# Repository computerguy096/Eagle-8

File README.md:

# Eagle-8: Pentium Pro for affordable boards

This is a Socket 8 to Slot 1 adapter (so called "slotket") which allows you to install Pentium Pro CPUs in Slot 1 motherboards. This project was mainly started because of the Socket 8 boards scarcity and limitations (no AGP bus, limited to EDO memory, etc) and being tired of having to deal with them. 

Features:
- AM3 bracket holes + 3D printed spacer (modern AM3 CPUs sit lower than the Pentium Pro, so it has to be adapted)
- spot for an optional NTC thermistor located right under the CPU package; it is connected to the J3 header at the top
- spot for an optional 3-pin fan header, fed from the +5V pin in the Slot 1 connector
- FSB jumper with the option to run the slotket at 100MHz bus speed
- BR1<->BR3 selection jumper, to allow dual CPU operation in 440BX boards

There is an interactive HTML BOM which you can find [here](kicad/bom/ibom.html)

Support is experimental at the moment, depending on which CPU you chose.

The Pentium II Overdrive will run on all boards, although it may need microcode updates.

The Pentium Pro (all models) varies depending on the platform.

A list of support for Award based boards (that I have tested so far):
- i440FX/440LX: runs out of the box if BIOS is older than 1998, may need microcodes
- VIA 693/ALi M1621: unlikely to run out of the box; most BIOSes are >=1998
- i440BX: has ACPI bugs, same problems as above
- i810/815: unlikely to run due to incompatible VRM spec, same problems as above

A few select ASUS boards received experimental patched BIOSes, which were kindly provided by Deniz Özmen on his [website](https://oezmen.eu/bios/), though keep in mind your mileage may vary.

For manufacturing, ENIG plating is highly recommended.

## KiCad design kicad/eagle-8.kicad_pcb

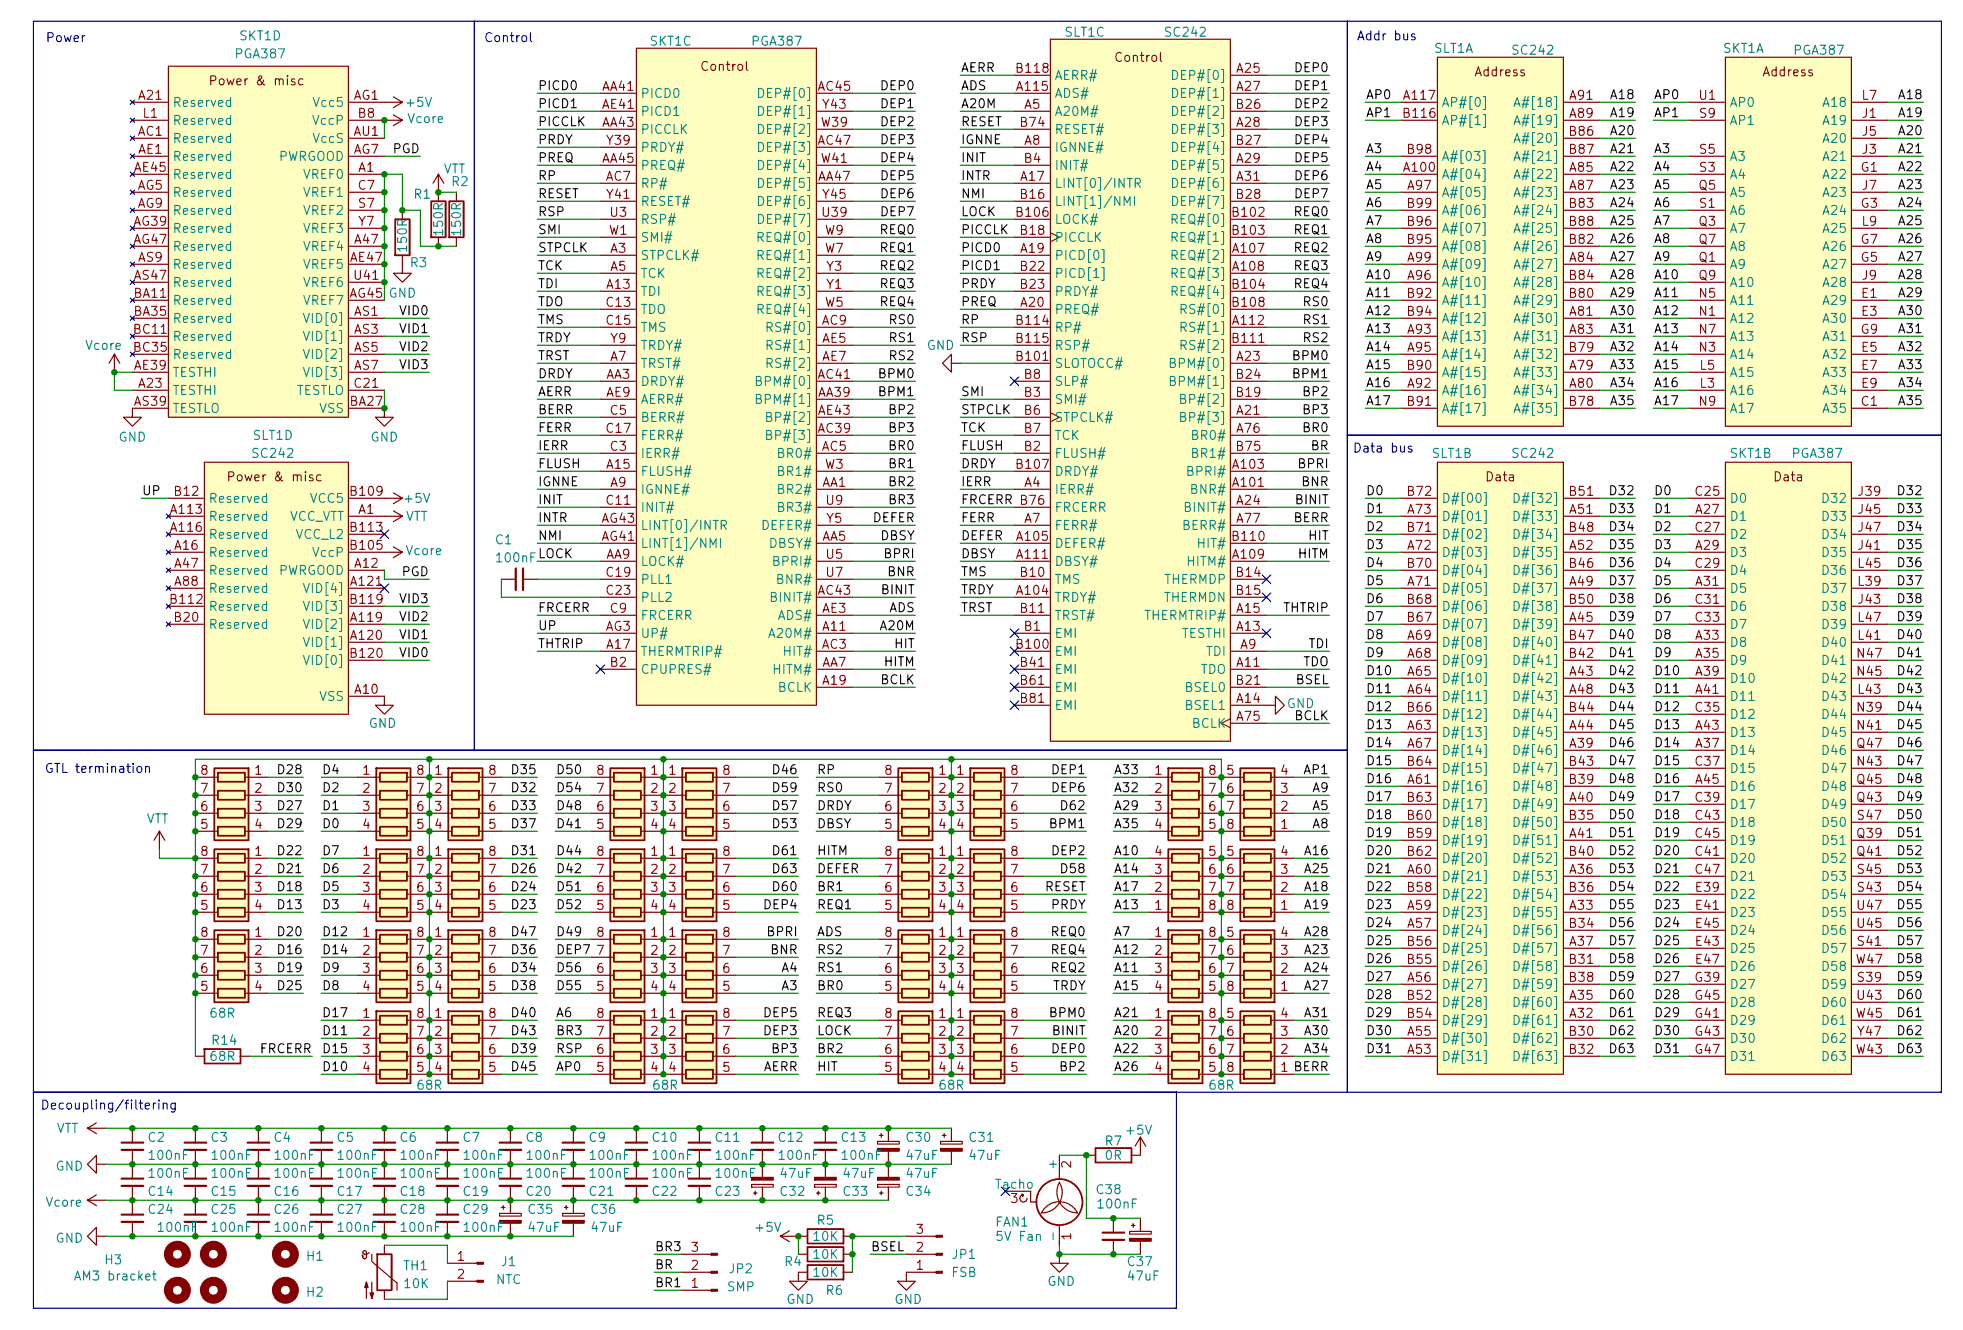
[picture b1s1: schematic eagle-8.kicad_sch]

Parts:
C1, C2: 100nF; C_0805_2012Metric; LCSC C1711
C3, C4, C5, C6, C7, C8, C9, C10, C11, C12, C13, C14, C15, C16, C17, C18, C19, C20, C21, C22, C23, C24, C25, C26, C27, C28, C29, C38: 100nF; C_0805_2012Metric
C30, C31, C32, C33, C34, C35, C37: 47uF; CP_EIA-7343-40_Kemet-Y_HandSolder
C36: 47uF; CP_EIA-7343-40_Kemet-Y_HandSolder; LCSC C600546
FAN1: 5V Fan; FanPinHeader_1x03_P2.54mm_Vertical
H1, H2: MountingHole; MountingHole_3.2mm_M3_DIN965
H3: AM3 bracket
J1: NTC; PinHeader_1x02_P2.54mm_Vertical
JP1: FSB; PinHeader_1x03_P2.54mm_Vertical
JP2: SMP; PinHeader_1x03_P2.54mm_Vertical
R1, R2, R3: 150R; R_0805_2012Metric; LCSC C17471
R4, R5, R6: 10K; R_0805_2012Metric; LCSC C17414
R7: 0R; R_0805_2012Metric; LCSC C17477
R14: 68R; R_0805_2012Metric; LCSC C17802
RN1, RN2, RN3, RN4, RN5, RN6, RN7, RN8, RN9, RN10, RN11, RN13, RN14, RN15, RN16, RN17, RN18, RN19, RN20, RN21, RN22, RN23, RN24, RN25, RN26, RN27, RN28, RN29, RN30, RN31, RN32, RN33, RN34, RN35: 68R; VTT array
RN12: 68R; VTT array; LCSC C429297
SKT1: PGA387
SLT1: SC242; Slot 1
TH1: 10K; PinHeader_1x02_P2.54mm_Vertical

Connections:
+5V: R4.1, R5.1, R7.2, SKT1.AG1 (Vcc5), SLT1.B109 (VCC5)
/A3: RN31.5 (R4.2), SKT1.S5 (A3), SLT1.B98 (A#[03])
/A4: RN31.6 (R3.2), SKT1.S3 (A4), SLT1.A100 (A#[04])
/A5: RN1.2 (R2.1), SKT1.Q5 (A5), SLT1.A97 (A#[05])
/A6: RN35.8 (R1.2), SKT1.S1 (A6), SLT1.B99 (A#[06])
/A7: RN4.1 (R1.1), SKT1.Q3 (A7), SLT1.B96 (A#[07])
/A8: RN1.1 (R1.1), SKT1.Q7 (A8), SLT1.B95 (A#[08])
/A9: RN1.3 (R3.1), SKT1.Q1 (A9), SLT1.A99 (A#[09])
/A10: RN2.4 (R4.1), SKT1.Q9 (A10), SLT1.A96 (A#[10])
/A11: RN4.3 (R3.1), SKT1.N5 (A11), SLT1.B92 (A#[11])
/A12: RN4.2 (R2.1), SKT1.N1 (A12), SLT1.B94 (A#[12])
/A13: RN2.1 (R1.1), SKT1.N7 (A13), SLT1.A93 (A#[13])
/A14: RN2.3 (R3.1), SKT1.N3 (A14), SLT1.A95 (A#[14])
/A15: RN4.4 (R4.1), SKT1.L5 (A15), SLT1.B90 (A#[15])
/A16: RN3.4 (R4.1), SKT1.L3 (A16), SLT1.A92 (A#[16])
/A17: RN2.2 (R2.1), SKT1.N9 (A17), SLT1.B91 (A#[17])
/A18: RN3.2 (R2.1), SKT1.L7 (A18), SLT1.A91 (A#[18])
/A19: RN3.1 (R1.1), SKT1.J1 (A19), SLT1.A89 (A#[19])
/A20: RN6.2 (R2.1), SKT1.J5 (A20), SLT1.B86 (A#[20])
/A20M: SKT1.A11 (A20M#), SLT1.A5 (A20M#)
/A21: RN6.1 (R1.1), SKT1.J3 (A21), SLT1.B87 (A#[21])
/A22: RN6.3 (R3.1), SKT1.G1 (A22), SLT1.A85 (A#[22])
/A23: RN5.3 (R3.1), SKT1.J7 (A23), SLT1.A87 (A#[23])
/A24: RN5.2 (R2.1), SKT1.G3 (A24), SLT1.B83 (A#[24])
/A25: RN3.3 (R3.1), SKT1.L9 (A25), SLT1.B88 (A#[25])
/A26: RN6.4 (R4.1), SKT1.G7 (A26), SLT1.B82 (A#[26])
/A27: RN5.1 (R1.1), SKT1.G5 (A27), SLT1.A84 (A#[27])
/A28: RN5.4 (R4.1), SKT1.J9 (A28), SLT1.B84 (A#[28])
/A29: RN24.3 (R3.1), SKT1.E1 (A29), SLT1.B80 (A#[29])
/A30: RN7.3 (R3.1), SKT1.E3 (A30), SLT1.A81 (A#[30])
/A31: RN7.4 (R4.1), SKT1.G9 (A31), SLT1.A83 (A#[31])
/A32: RN24.2 (R2.1), SKT1.E5 (A32), SLT1.B79 (A#[32])
/A33: RN24.1 (R1.1), SKT1.E7 (A33), SLT1.A79 (A#[33])
/A34: RN7.2 (R2.1), SKT1.E9 (A34), SLT1.A80 (A#[34])
/A35: RN24.4 (R4.1), SKT1.C1 (A35), SLT1.B78 (A#[35])
/ADS: RN29.8 (R1.2), SKT1.AE3 (ADS#), SLT1.A115 (ADS#)
/AERR: RN32.5 (R4.2), SKT1.AE9 (AERR#), SLT1.B118 (AERR#)
/AP0: RN35.5 (R4.2), SKT1.U1 (AP0), SLT1.A117 (AP#[0])
/AP1: RN1.4 (R4.1), SKT1.S9 (AP1), SLT1.B116 (AP#[1])
/BCLK: SKT1.A19 (BCLK), SLT1.A75 (BCLK)
/BERR: RN7.1 (R1.1), SKT1.C5 (BERR#), SLT1.A77 (BERR#)
/BINIT: RN28.7 (R2.2), SKT1.AC43 (BINIT#), SLT1.A24 (BINIT#)
/BNR: RN31.7 (R2.2), SKT1.U7 (BNR#), SLT1.A101 (BNR#)
/BP2: RN28.5 (R4.2), SKT1.AE43 (BP#[2]), SLT1.B19 (BP#[2])
/BP3: RN32.6 (R3.2), SKT1.AC39 (BP#[3]), SLT1.A21 (BP#[3])
/BPM0: RN28.8 (R1.2), SKT1.AC41 (BPM#[0]), SLT1.A23 (BPM#[0])
/BPM1: RN25.5 (R4.2), SKT1.AA39 (BPM#[1]), SLT1.B24 (BPM#[1])
/BPRI: RN31.8 (R1.2), SKT1.U5 (BPRI#), SLT1.A103 (BPRI#)
/BR: JP2.2, SLT1.B75 (BR1#)
/BR0: RN29.5 (R4.2), SKT1.AC5 (BR0#), SLT1.A76 (BR0#)
/BR1: JP2.1, RN34.6 (R3.2), SKT1.W3 (BR1#)
/BR2: RN30.6 (R3.2), SKT1.AA1 (BR2#)
/BR3: JP2.3, RN35.7 (R2.2), SKT1.U9 (BR3#)
/BSEL: JP1.2, SLT1.B21 (BSEL0)
/D0: RN8.4 (R4.1), SKT1.C25 (D0), SLT1.B72 (D#[00])
/D1: RN8.3 (R3.1), SKT1.A27 (D1), SLT1.A73 (D#[01])
/D2: RN8.2 (R2.1), SKT1.C27 (D2), SLT1.B71 (D#[02])
/D3: RN9.4 (R4.1), SKT1.A29 (D3), SLT1.A72 (D#[03])
/D4: RN8.1 (R1.1), SKT1.C29 (D4), SLT1.B70 (D#[04])
/D5: RN9.3 (R3.1), SKT1.A31 (D5), SLT1.A71 (D#[05])
/D6: RN9.2 (R2.1), SKT1.C31 (D6), SLT1.B68 (D#[06])
/D7: RN9.1 (R1.1), SKT1.C33 (D7), SLT1.B67 (D#[07])
/D8: RN10.4 (R4.1), SKT1.A33 (D8), SLT1.A69 (D#[08])
/D9: RN10.3 (R3.1), SKT1.A35 (D9), SLT1.A68 (D#[09])
/D10: RN11.4 (R4.1), SKT1.A39 (D10), SLT1.A65 (D#[10])
/D11: RN11.2 (R2.1), SKT1.A41 (D11), SLT1.A64 (D#[11])
/D12: RN10.1 (R1.1), SKT1.C35 (D12), SLT1.B66 (D#[12])
/D13: RN13.4 (R4.1), SKT1.A43 (D13), SLT1.A63 (D#[13])
/D14: RN10.2 (R2.1), SKT1.A37 (D14), SLT1.A67 (D#[14])
/D15: RN11.3 (R3.1), SKT1.C37 (D15), SLT1.B64 (D#[15])
/D16: RN14.2 (R2.1), SKT1.A45 (D16), SLT1.A61 (D#[16])
/D17: RN11.1 (R1.1), SKT1.C39 (D17), SLT1.B63 (D#[17])
/D18: RN13.3 (R3.1), SKT1.C43 (D18), SLT1.B60 (D#[18])
/D19: RN14.3 (R3.1), SKT1.C45 (D19), SLT1.B59 (D#[19])
/D20: RN14.1 (R1.1), SKT1.C41 (D20), SLT1.B62 (D#[20])
/D21: RN13.2 (R2.1), SKT1.C47 (D21), SLT1.A60 (D#[21])
/D22: RN13.1 (R1.1), SKT1.E39 (D22), SLT1.B58 (D#[22])
/D23: RN16.5 (R4.2), SKT1.E41 (D23), SLT1.A59 (D#[23])
/D24: RN16.6 (R3.2), SKT1.E45 (D24), SLT1.A57 (D#[24])
/D25: RN14.4 (R4.1), SKT1.E43 (D25), SLT1.B56 (D#[25])
/D26: RN16.7 (R2.2), SKT1.E47 (D26), SLT1.B55 (D#[26])
/D27: RN12.3 (R3.1), SKT1.G39 (D27), SLT1.A56 (D#[27])
/D28: RN12.1 (R1.1), SKT1.G45 (D28), SLT1.B52 (D#[28])
/D29: RN12.4 (R4.1), SKT1.G41 (D29), SLT1.B54 (D#[29])
/D30: RN12.2 (R2.1), SKT1.G43 (D30), SLT1.A55 (D#[30])
/D31: RN16.8 (R1.2), SKT1.G47 (D31), SLT1.A53 (D#[31])
/D32: RN15.7 (R2.2), SKT1.J39 (D32), SLT1.B51 (D#[32])
/D33: RN15.6 (R3.2), SKT1.J45 (D33), SLT1.A51 (D#[33])
/D34: RN17.6 (R3.2), SKT1.J47 (D34), SLT1.B48 (D#[34])
/D35: RN15.8 (R1.2), SKT1.J41 (D35), SLT1.A52 (D#[35])
/D36: RN17.7 (R2.2), SKT1.L45 (D36), SLT1.B46 (D#[36])
/D37: RN15.5 (R4.2), SKT1.L39 (D37), SLT1.A49 (D#[37])
/D38: RN17.5 (R4.2), SKT1.J43 (D38), SLT1.B50 (D#[38])
/D39: RN18.6 (R3.2), SKT1.L47 (D39), SLT1.A45 (D#[39])
/D40: RN18.8 (R1.2), SKT1.L41 (D40), SLT1.B47 (D#[40])
/D41: RN19.5 (R4.2), SKT1.N47 (D41), SLT1.B42 (D#[41])
/D42: RN20.7 (R2.2), SKT1.N45 (D42), SLT1.A43 (D#[42])
/D43: RN18.7 (R2.2), SKT1.L43 (D43), SLT1.A48 (D#[43])
/D44: RN20.8 (R1.2), SKT1.N39 (D44), SLT1.B44 (D#[44])
/D45: RN18.5 (R4.2), SKT1.N41 (D45), SLT1.A44 (D#[45])
/D46: RN22.8 (R1.2), SKT1.Q47 (D46), SLT1.A39 (D#[46])
/D47: RN17.8 (R1.2), SKT1.N43 (D47), SLT1.B43 (D#[47])
/D48: RN19.6 (R3.2), SKT1.Q45 (D48), SLT1.B39 (D#[48])
/D49: RN21.8 (R1.2), SKT1.Q43 (D49), SLT1.A40 (D#[49])
/D50: RN19.8 (R1.2), SKT1.S47 (D50), SLT1.B35 (D#[50])
/D51: RN20.6 (R3.2), SKT1.Q39 (D51), SLT1.A41 (D#[51])
/D52: RN20.5 (R4.2), SKT1.Q41 (D52), SLT1.B40 (D#[52])
/D53: RN22.5 (R4.2), SKT1.S45 (D53), SLT1.A36 (D#[53])
/D54: RN19.7 (R2.2), SKT1.S43 (D54), SLT1.B36 (D#[54])
/D55: RN21.5 (R4.2), SKT1.U47 (D55), SLT1.A33 (D#[55])
/D56: RN21.6 (R3.2), SKT1.U45 (D56), SLT1.B34 (D#[56])
/D57: RN22.6 (R3.2), SKT1.S41 (D57), SLT1.A37 (D#[57])
/D58: RN26.7 (R2.2), SKT1.W47 (D58), SLT1.B31 (D#[58])
/D59: RN22.7 (R2.2), SKT1.S39 (D59), SLT1.B38 (D#[59])
/D60: RN23.6 (R3.2), SKT1.U43 (D60), SLT1.A35 (D#[60])
/D61: RN23.8 (R1.2), SKT1.W45 (D61), SLT1.A32 (D#[61])
/D62: RN25.6 (R3.2), SKT1.Y47 (D62), SLT1.B30 (D#[62])
/D63: RN23.7 (R2.2), SKT1.W43 (D63), SLT1.B32 (D#[63])
/DBSY: RN33.5 (R4.2), SKT1.AA5 (DBSY#), SLT1.A111 (DBSY#)
/DEFER: RN34.7 (R2.2), SKT1.Y5 (DEFER#), SLT1.A105 (DEFER#)
/DEP0: RN28.6 (R3.2), SKT1.AC45 (DEP#[0]), SLT1.A25 (DEP#[0])
/DEP1: RN25.8 (R1.2), SKT1.Y43 (DEP#[1]), SLT1.A27 (DEP#[1])
/DEP2: RN26.8 (R1.2), SKT1.W39 (DEP#[2]), SLT1.B26 (DEP#[2])
/DEP3: RN32.7 (R2.2), SKT1.AC47 (DEP#[3]), SLT1.A28 (DEP#[3])
/DEP4: RN23.5 (R4.2), SKT1.W41 (DEP#[4]), SLT1.B27 (DEP#[4])
/DEP5: RN32.8 (R1.2), SKT1.AA47 (DEP#[5]), SLT1.A29 (DEP#[5])
/DEP6: RN25.7 (R2.2), SKT1.Y45 (DEP#[6]), SLT1.A31 (DEP#[6])
/DEP7: RN21.7 (R2.2), SKT1.U39 (DEP#[7]), SLT1.B28 (DEP#[7])
/DRDY: RN33.6 (R3.2), SKT1.AA3 (DRDY#), SLT1.B107 (DRDY#)
/FERR: SKT1.C17 (FERR#), SLT1.A7 (FERR#)
/FLUSH: SKT1.A15 (FLUSH#), SLT1.B2 (FLUSH#)
/FRCERR: R14.1, SKT1.C9 (FRCERR), SLT1.B76 (FRCERR)
/HIT: RN30.5 (R4.2), SKT1.AC3 (HIT#), SLT1.B110 (HIT#)
/HITM: RN34.8 (R1.2), SKT1.AA7 (HITM#), SLT1.A109 (HITM#)
/IERR: SKT1.C3 (IERR#), SLT1.A4 (IERR#)
/IGNNE: SKT1.A9 (IGNNE#), SLT1.A8 (IGNNE#)
/INIT: SKT1.C11 (INIT#), SLT1.B4 (INIT#)
/INTR: SKT1.AG43 (LINT[0]/INTR), SLT1.A17 (LINT[0]/INTR)
/LOCK: RN30.7 (R2.2), SKT1.AA9 (LOCK#), SLT1.B106 (LOCK#)
/NMI: SKT1.AG41 (LINT[1]/NMI), SLT1.B16 (LINT[1]/NMI)
/PGD: SKT1.AG7 (PWRGOOD), SLT1.A12 (PWRGOOD)
/PICCLK: SKT1.AA43 (PICCLK), SLT1.B18 (PICCLK)
/PICD0: SKT1.AA41 (PICD0), SLT1.A19 (PICD[0])
/PICD1: SKT1.AE41 (PICD1), SLT1.B22 (PICD[1])
/PRDY: RN26.5 (R4.2), SKT1.Y39 (PRDY#), SLT1.B23 (PRDY#)
/PREQ: SKT1.AA45 (PREQ#), SLT1.A20 (PREQ#)
/REQ0: RN27.8 (R1.2), SKT1.W9 (REQ#[0]), SLT1.B102 (REQ#[0])
/REQ1: RN34.5 (R4.2), SKT1.W7 (REQ#[1]), SLT1.B103 (REQ#[1])
/REQ2: RN27.6 (R3.2), SKT1.Y3 (REQ#[2]), SLT1.A107 (REQ#[2])
/REQ3: RN30.8 (R1.2), SKT1.Y1 (REQ#[3]), SLT1.A108 (REQ#[3])
/REQ4: RN27.7 (R2.2), SKT1.W5 (REQ#[4]), SLT1.B104 (REQ#[4])
/RESET: RN26.6 (R3.2), SKT1.Y41 (RESET#), SLT1.B74 (RESET#)
/RP: RN33.8 (R1.2), SKT1.AC7 (RP#), SLT1.B114 (RP#)
/RS0: RN33.7 (R2.2), SKT1.AC9 (RS#[0]), SLT1.B108 (RS#[0])
/RS1: RN29.6 (R3.2), SKT1.AE5 (RS#[1]), SLT1.A112 (RS#[1])
/RS2: RN29.7 (R2.2), SKT1.AE7 (RS#[2]), SLT1.B111 (RS#[2])
/RSP: RN35.6 (R3.2), SKT1.U3 (RSP#), SLT1.B115 (RSP#)
/SMI: SKT1.W1 (SMI#), SLT1.B3 (SMI#)
/STPCLK: SKT1.A3 (STPCLK#), SLT1.B6 (STPCLK#)
/TCK: SKT1.A5 (TCK), SLT1.B7 (TCK)
/TDI: SKT1.A13 (TDI), SLT1.A9 (TDI)
/TDO: SKT1.C13 (TDO), SLT1.A11 (TDO)
/THTRIP: SKT1.A17 (THERMTRIP#), SLT1.A15 (THERMTRIP#)
/TMS: SKT1.C15 (TMS), SLT1.B10 (TMS)
/TRDY: RN27.5 (R4.2), SKT1.Y9 (TRDY#), SLT1.A104 (TRDY#)
/TRST: SKT1.A7 (TRST#), SLT1.B11 (TRST#)
/UP: SKT1.AG3 (UP#), SLT1.B12 (Reserved)
/VID0: SKT1.AS1 (VID[0]), SLT1.B120 (VID[0])
/VID1: SKT1.AS3 (VID[1]), SLT1.A120 (VID[1])
/VID2: SKT1.AS5 (VID[2]), SLT1.A119 (VID[2])
/VID3: SKT1.AS7 (VID[3]), SLT1.B119 (VID[3])
GND: C2.1, C3.1, C4.1, C5.1, C6.1, C7.1, C8.1, C9.1, C10.1, C11.1, C12.1, C13.1, C14.1, C15.1, C16.1, C17.1, C18.1, C19.1, C20.1, C21.1, C22.1, C23.1, C24.1, C25.1, C26.1, C27.1, C28.1, C29.1, C30.2, C31.2, C32.2, C33.2, C34.2, C35.2, C36.2, C37.2, C38.1, FAN1.1 (-), JP1.1, R3.2, R6.1, SKT1.AB2 (VSS), SKT1.AB6 (VSS), SKT1.AB8 (VSS), SKT1.AB40 (VSS), SKT1.AB42 (VSS), SKT1.AB46 (VSS), SKT1.AF2 (VSS), SKT1.AF4 (VSS), SKT1.AF6 (VSS), SKT1.AF8 (VSS), SKT1.AF40 (VSS), SKT1.AF42 (VSS), SKT1.AF44 (VSS), SKT1.AF46 (VSS), SKT1.AJ1 (VSS), SKT1.AJ5 (VSS), SKT1.AJ9 (VSS), SKT1.AJ39 (VSS), SKT1.AJ43 (VSS), SKT1.AJ47 (VSS), SKT1.AL3 (VSS), SKT1.AL7 (VSS), SKT1.AL41 (VSS), SKT1.AL45 (VSS), SKT1.AN1 (VSS), SKT1.AN5 (VSS), SKT1.AN9 (VSS), SKT1.AN39 (VSS), SKT1.AN43 (VSS), SKT1.AN47 (VSS), SKT1.AQ3 (VSS), SKT1.AQ7 (VSS), SKT1.AQ41 (VSS), SKT1.AQ45 (VSS), SKT1.AS39 (TESTLO), SKT1.AS41 (TESTLO), SKT1.AS43 (TESTLO), SKT1.AS45 (TESTLO), SKT1.AU3 (VSS), SKT1.AU7 (VSS), SKT1.AU41 (VSS), SKT1.AU45 (VSS), SKT1.AW1 (VSS), SKT1.AW5 (VSS), SKT1.AW9 (VSS), SKT1.AW39 (VSS), SKT1.AW43 (VSS), SKT1.AW47 (VSS), SKT1.B6 (VSS), SKT1.B12 (VSS), SKT1.B20 (VSS), SKT1.B28 (VSS), SKT1.B36 (VSS), SKT1.B42 (VSS), SKT1.B46 (VSS), SKT1.BA1 (VSS), SKT1.BA5 (VSS), SKT1.BA9 (VSS), SKT1.BA13 (TESTLO), SKT1.BA15 (TESTLO), SKT1.BA19 (VSS), SKT1.BA23 (VSS), SKT1.BA27 (VSS), SKT1.BA31 (VSS), SKT1.BA33 (TESTLO), SKT1.BA37 (TESTLO), SKT1.BA39 (VSS), SKT1.BA43 (VSS), SKT1.BA47 (VSS), SKT1.BC1 (VSS), SKT1.BC3 (VSS), SKT1.BC5 (VSS), SKT1.BC7 (VSS), SKT1.BC9 (VSS), SKT1.BC13 (TESTLO), SKT1.BC15 (TESTLO), SKT1.BC17 (VSS), SKT1.BC21 (VSS), SKT1.BC25 (VSS), SKT1.BC29 (VSS), SKT1.BC33 (TESTLO), SKT1.BC37 (TESTLO), SKT1.BC39 (VSS), SKT1.BC41 (VSS), SKT1.BC43 (VSS), SKT1.BC45 (VSS), SKT1.BC47 (VSS), SKT1.C21 (TESTLO), SKT1.F4 (VSS), SKT1.F8 (VSS), SKT1.F40 (VSS), SKT1.F44 (VSS), SKT1.K2 (VSS), SKT1.K6 (VSS), SKT1.K8 (VSS), SKT1.K40 (VSS), SKT1.K42 (VSS), SKT1.K46 (VSS), SKT1.P4 (VSS), SKT1.P8 (VSS), SKT1.P40 (VSS), SKT1.P44 (VSS), SKT1.T2 (VSS), SKT1.T6 (VSS), SKT1.T8 (VSS), SKT1.T40 (VSS), SKT1.T42 (VSS), SKT1.T46 (VSS), SKT1.X2 (VSS), SKT1.X4 (VSS), SKT1.X8 (VSS), SKT1.X40 (VSS), SKT1.X44 (VSS), SKT1.X46 (VSS), SLT1.A2 (VSS), SLT1.A6 (VSS), SLT1.A10 (VSS), SLT1.A14 (BSEL1), SLT1.A18 (VSS), SLT1.A22 (VSS), SLT1.A26 (VSS), SLT1.A30 (VSS), SLT1.A34 (VSS), SLT1.A38 (VSS), SLT1.A42 (VSS), SLT1.A46 (VSS), SLT1.A50 (VSS), SLT1.A54 (VSS), SLT1.A58 (VSS), SLT1.A62 (VSS), SLT1.A66 (VSS), SLT1.A70 (VSS), SLT1.A74 (VSS), SLT1.A78 (VSS), SLT1.A82 (VSS), SLT1.A86 (VSS), SLT1.A90 (VSS), SLT1.A94 (VSS), SLT1.A98 (VSS), SLT1.A102 (VSS), SLT1.A106 (VSS), SLT1.A110 (VSS), SLT1.A114 (VSS), SLT1.A118 (VSS), SLT1.B101 (SLOTOCC#)
unnamed: C37.1, C38.2, FAN1.2 (+), R7.1
unnamed: J1.1, TH1.1
unnamed: J1.2, TH1.2
unnamed: JP1.3, R4.2, R5.2, R6.2
unnamed: C1.2, SKT1.C19 (PLL1)
unnamed: C1.1, SKT1.C23 (PLL2)
unnamed: R1.2, R2.2, R3.1, SKT1.A1 (VREF0), SKT1.A47 (VREF4), SKT1.AE47 (VREF5), SKT1.AG45 (VREF7), SKT1.C7 (VREF1), SKT1.S7 (VREF2), SKT1.U41 (VREF6), SKT1.Y7 (VREF3)
VTT: C2.2, C3.2, C4.2, C5.2, C6.2, C7.2, C8.2, C9.2, C10.2, C11.2, C12.2, C13.2, C30.1, C31.1, R1.1, R2.1, R14.2, RN1.5 (R4.2), RN1.6 (R3.2), RN1.7 (R2.2), RN1.8 (R1.2), RN2.5 (R4.2), RN2.6 (R3.2), RN2.7 (R2.2), RN2.8 (R1.2), RN3.5 (R4.2), RN3.6 (R3.2), RN3.7 (R2.2), RN3.8 (R1.2), RN4.5 (R4.2), RN4.6 (R3.2), RN4.7 (R2.2), RN4.8 (R1.2), RN5.5 (R4.2), RN5.6 (R3.2), RN5.7 (R2.2), RN5.8 (R1.2), RN6.5 (R4.2), RN6.6 (R3.2), RN6.7 (R2.2), RN6.8 (R1.2), RN7.5 (R4.2), RN7.6 (R3.2), RN7.7 (R2.2), RN7.8 (R1.2), RN8.5 (R4.2), RN8.6 (R3.2), RN8.7 (R2.2), RN8.8 (R1.2), RN9.5 (R4.2), RN9.6 (R3.2), RN9.7 (R2.2), RN9.8 (R1.2), RN10.5 (R4.2), RN10.6 (R3.2), RN10.7 (R2.2), RN10.8 (R1.2), RN11.5 (R4.2), RN11.6 (R3.2), RN11.7 (R2.2), RN11.8 (R1.2), RN12.5 (R4.2), RN12.6 (R3.2), RN12.7 (R2.2), RN12.8 (R1.2), RN13.5 (R4.2), RN13.6 (R3.2), RN13.7 (R2.2), RN13.8 (R1.2), RN14.5 (R4.2), RN14.6 (R3.2), RN14.7 (R2.2), RN14.8 (R1.2), RN15.1 (R1.1), RN15.2 (R2.1), RN15.3 (R3.1), RN15.4 (R4.1), RN16.1 (R1.1), RN16.2 (R2.1), RN16.3 (R3.1), RN16.4 (R4.1), RN17.1 (R1.1), RN17.2 (R2.1), RN17.3 (R3.1), RN17.4 (R4.1), RN18.1 (R1.1), RN18.2 (R2.1), RN18.3 (R3.1), RN18.4 (R4.1), RN19.1 (R1.1), RN19.2 (R2.1), RN19.3 (R3.1), RN19.4 (R4.1), RN20.1 (R1.1), RN20.2 (R2.1), RN20.3 (R3.1), RN20.4 (R4.1), RN21.1 (R1.1), RN21.2 (R2.1), RN21.3 (R3.1), RN21.4 (R4.1), RN22.1 (R1.1), RN22.2 (R2.1), RN22.3 (R3.1), RN22.4 (R4.1), RN23.1 (R1.1), RN23.2 (R2.1), RN23.3 (R3.1), RN23.4 (R4.1), RN24.5 (R4.2), RN24.6 (R3.2), RN24.7 (R2.2), RN24.8 (R1.2), RN25.1 (R1.1), RN25.2 (R2.1), RN25.3 (R3.1), RN25.4 (R4.1), RN26.1 (R1.1), RN26.2 (R2.1), RN26.3 (R3.1), RN26.4 (R4.1), RN27.1 (R1.1), RN27.2 (R2.1), RN27.3 (R3.1), RN27.4 (R4.1), RN28.1 (R1.1), RN28.2 (R2.1), RN28.3 (R3.1), RN28.4 (R4.1), RN29.1 (R1.1), RN29.2 (R2.1), RN29.3 (R3.1), RN29.4 (R4.1), RN30.1 (R1.1), RN30.2 (R2.1), RN30.3 (R3.1), RN30.4 (R4.1), RN31.1 (R1.1), RN31.2 (R2.1), RN31.3 (R3.1), RN31.4 (R4.1), RN32.1 (R1.1), RN32.2 (R2.1), RN32.3 (R3.1), RN32.4 (R4.1), RN33.1 (R1.1), RN33.2 (R2.1), RN33.3 (R3.1), RN33.4 (R4.1), RN34.1 (R1.1), RN34.2 (R2.1), RN34.3 (R3.1), RN34.4 (R4.1), RN35.1 (R1.1), RN35.2 (R2.1), RN35.3 (R3.1), RN35.4 (R4.1), SLT1.A1 (VCC_VTT), SLT1.A3 (VCC_VTT), SLT1.B5 (VCC_VTT), SLT1.B9 (VCC_VTT)
Vcore: C14.2, C15.2, C16.2, C17.2, C18.2, C19.2, C20.2, C21.2, C22.2, C23.2, C24.2, C25.2, C26.2, C27.2, C28.2, C29.2, C32.1, C33.1, C34.1, C35.1, C36.1, SKT1.A23 (TESTHI), SKT1.A25 (TESTHI), SKT1.AB4 (VccP), SKT1.AB44 (VccP), SKT1.AE39 (TESTHI), SKT1.AJ3 (VccP), SKT1.AJ7 (VccP), SKT1.AJ41 (VccP), SKT1.AJ45 (VccP), SKT1.AL1 (VccP), SKT1.AL5 (VccP), SKT1.AL9 (VccP), SKT1.AL39 (VccP), SKT1.AL43 (VccP), SKT1.AL47 (VccP), SKT1.AN3 (VccP), SKT1.AN7 (VccP), SKT1.AN41 (VccP), SKT1.AN45 (VccP), SKT1.AQ1 (VccP), SKT1.AQ5 (VccP), SKT1.AQ9 (VccP), SKT1.AQ39 (VccP), SKT1.AQ43 (VccP), SKT1.AQ47 (VccP), SKT1.AU1 (VccS), SKT1.AU5 (VccS), SKT1.AU9 (VccS), SKT1.AU39 (VccS), SKT1.AU43 (VccS), SKT1.AU47 (VccS), SKT1.AW3 (VccS), SKT1.AW7 (VccS), SKT1.AW41 (VccS), SKT1.AW45 (VccS), SKT1.AY1 (VccS), SKT1.AY3 (VccS), SKT1.AY5 (VccS), SKT1.AY7 (VccS), SKT1.AY9 (VccS), SKT1.AY39 (VccS), SKT1.AY41 (VccS), SKT1.AY43 (VccS), SKT1.AY45 (VccS), SKT1.AY47 (VccS), SKT1.B4 (VccP), SKT1.B8 (VccP), SKT1.B16 (VccP), SKT1.B24 (VccP), SKT1.B32 (VccP), SKT1.B40 (VccP), SKT1.B44 (VccP), SKT1.BA3 (VccS), SKT1.BA7 (VccS), SKT1.BA17 (VccP), SKT1.BA21 (VccP), SKT1.BA25 (VccP), SKT1.BA29 (VccP), SKT1.BA41 (VccS), SKT1.BA45 (VccS), SKT1.BC19 (VccS), SKT1.BC23 (VccS), SKT1.BC27 (VccS), SKT1.BC31 (VccS), SKT1.F2 (VccP), SKT1.F6 (VccP), SKT1.F42 (VccP), SKT1.F46 (VccP), SKT1.K4 (VccP), SKT1.K44 (VccP), SKT1.P2 (VccP), SKT1.P6 (VccP), SKT1.P42 (VccP), SKT1.P46 (VccP), SKT1.T4 (VccP), SKT1.T44 (VccP), SKT1.X6 (VccP), SKT1.X42 (VccP), SLT1.B13 (VccP), SLT1.B17 (VccP), SLT1.B25 (VccP), SLT1.B29 (VccP), SLT1.B33 (VccP), SLT1.B37 (VccP), SLT1.B45 (VccP), SLT1.B49 (VccP), SLT1.B53 (VccP), SLT1.B57 (VccP), SLT1.B65 (VccP), SLT1.B69 (VccP), SLT1.B73 (VccP), SLT1.B77 (VccP), SLT1.B85 (VccP), SLT1.B89 (VccP), SLT1.B93 (VccP), SLT1.B97 (VccP), SLT1.B105 (VccP)

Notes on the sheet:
Control
GTL termination
Data bus
Decoupling/filtering
Power
Addr bus

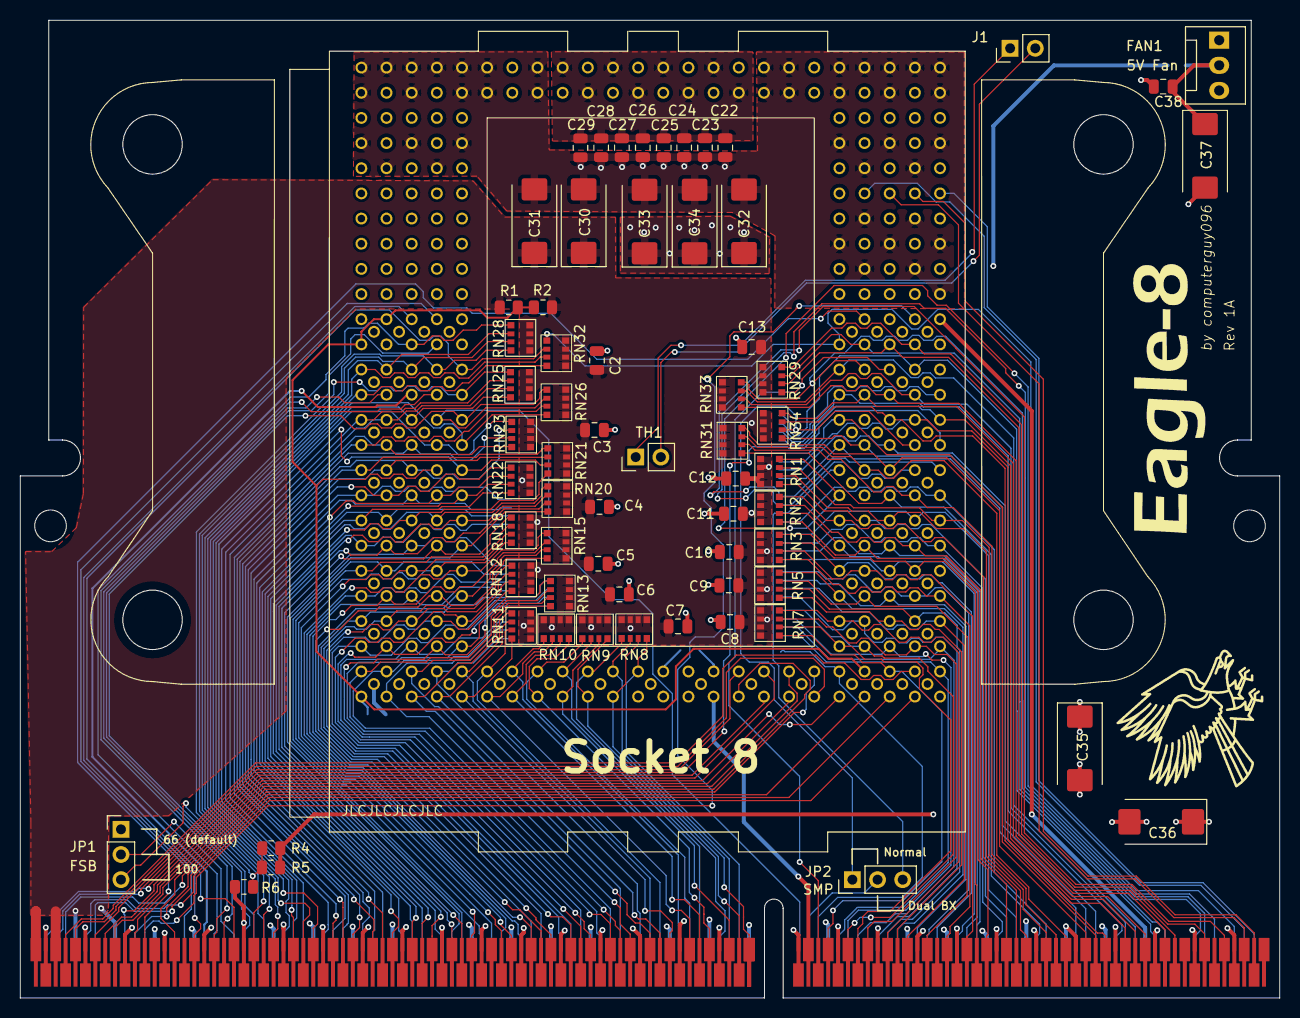
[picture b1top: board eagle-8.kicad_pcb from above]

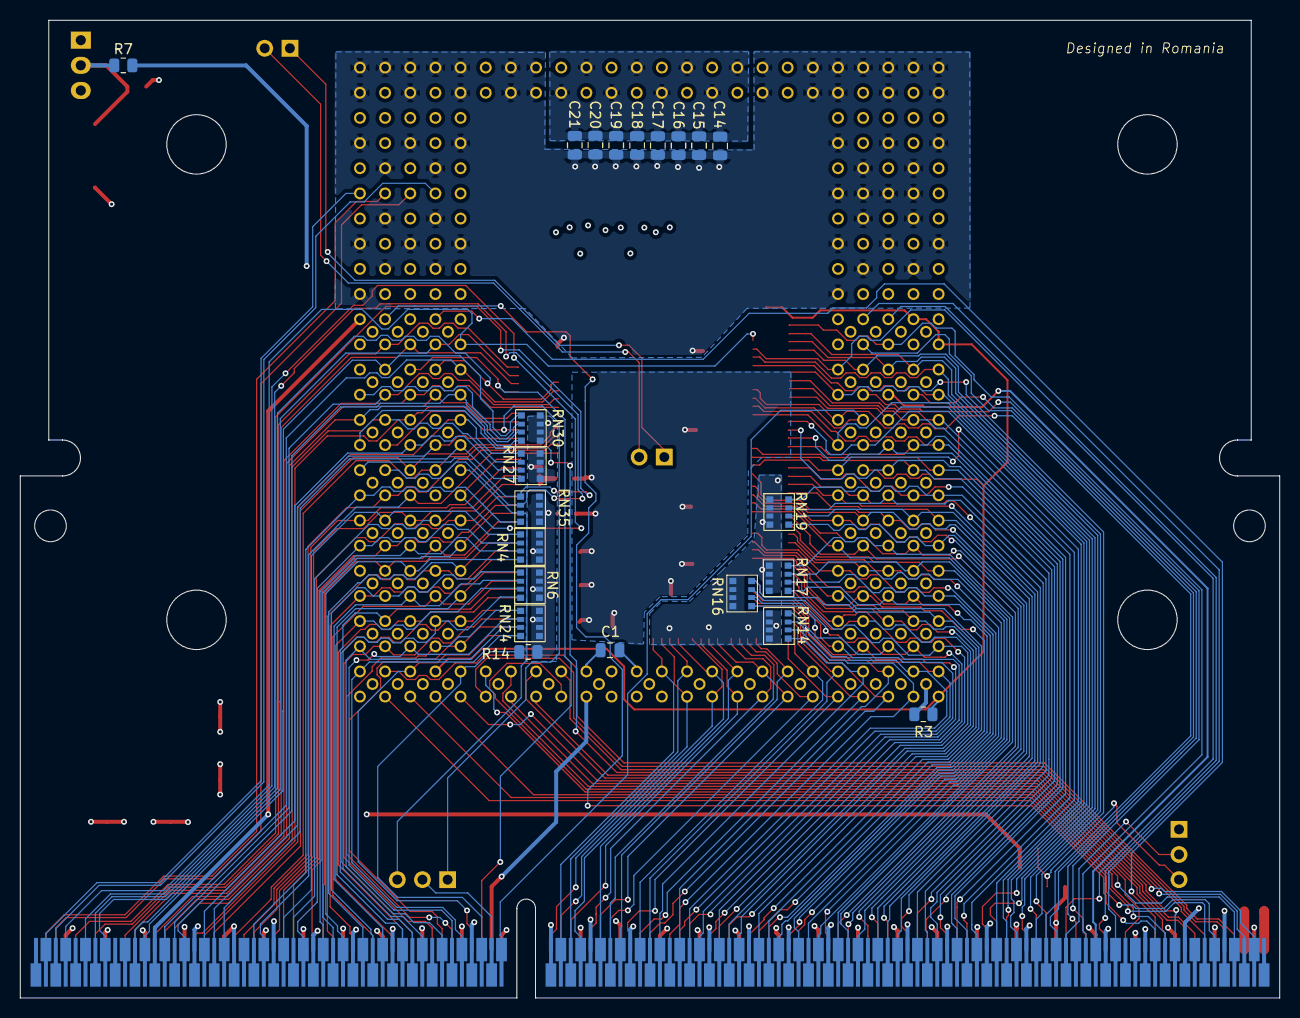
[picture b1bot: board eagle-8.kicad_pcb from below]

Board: 4 copper layers, 127.1 x 98.7 mm, 91 parts (22 on the bottom side), 181 nets.
